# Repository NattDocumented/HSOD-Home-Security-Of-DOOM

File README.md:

# H.S.O.D. : Home Security Of DOOM

A simple home security alarm with personality and a little twist ***wink*** ***wink***.

## What is it?

It is just like your simple, ordinary home security/alarm system. If you input your PIN to arm or disarm the alarm, and if you proceed to enter your PIN just in time, the alarm won't go off. However, when H.S.O.D went off... It doesn't just play a normal alarm... I will scare the burglar away (hopefully)... it plays a pre-recorded audio which you can customize/add custom audio to your liking, of how you would like to torment your burglar.

My personal option is DOOM ETERNAL MUSIC INTRO with + "so you are the chosen one."

## How do you use it?

It is very simple, here's how to use it!

### 1. Arming the Device
* **Action:** On boot, the system is disarmed. Input the PIN.
* **Outcome:** The current state of the device will change from unarmed to armed, and the OLED display and an audio cue from the speaker will indicate that!

### 2. INTRUDER ALERT!!!
* **Action:** Human detected.
* **Outcome:** The device enters a warning state or a countdown state, to be exact. The OLED display and a countdown coming from the speaker tracking your remaining time will also indicate that!

### 3. Disarming the Device
* **Action:** Input the PIN.
* **Outcome:**
  * **Correct PIN:** Everything resets and goes back to normal (back to the unarmed/disarmed state), the OLED display and the sound cue will also indicate it as well!
  * **Incorrect PIN:** Everything continues, but you can still go ahead and try again until the countdown reaches zero (but there's also a max attempt)

## System Architecture

```mermaid

graph TD;
  %%Define styles
  classDef controller fill:
  classDef sensor fill:
  classDef output fill:
  classDef cloud fill:

  %% Nodes
  Radar[HLK-LD2410C]:::sensor
  Mic[ICS-43434]:::sensor
  Keypad[Keypad]:::sensor

  MCU[Arduino Nano ESP32]:::controller

  OLED[OLED Display]:::output
  DFPlayer[DFPlayer Mini + Speaker]:::output

  Wit[Wit.ai Speech API]:::cloud

  %% Connections
  Radar --> |UART2 / Pin D11 Trigger| MCU
  Mic --> | I2S Mono PCM via DMA | MCU
  Keypad --> |Digital I/O Pins 2-8| MCU

  MCU --> |Hardware I2C| OLED
  MCU --> |Hardware UART1| DFPlayer
  MCU -.-> |Chunked HTTPS POST| Wit

```

## State Machine

```mermaid

stateDiagram-v2
  [*] --> STATE_DISARMED : Boot

  STATE_DISARMED --> STATE_ARMED : Enter PIN + ENT

  STATE_ARMED --> STATE_COUNTDOWN : Human Detected

  STATE_COUNTDOWN --> STATE_DISARMED : Correct PIN / Voice Phrase <br> Entered 
  STATE_COUNTDOWN --> STATE_ALARM : Timer Hits 0

  STATE_ALARM --> STATE_DISARMED : Correct PIN / Voice Phrase <br> Entered 
  STATE_ALARM --> STATE_LOCKED_OUT : Too Many Failed Attempts

  STATE_LOCKED_OUT --> STATE_ARMED  

```

## Why did I make it?

Here's a little back story. I passed an entrance exam to one of the best high schools in Thailand (Triam Udom Suksa School, btw ***wink*** ***wink***), which means I have to move away and live alone in the big city, but, being a country boy, I came up with an idea. Wouldn't it be so fitting to add some security measures to my apartment because I'm living alone? Normal Securities are boring, corporate, no personality, there's nothing interesting, so I came up with something new of my own! I came up with this!

## Step-By-Step Build Guide.

### Tools Required
* **Soldering Iron & Solder Wire** 
* **Wire Flush Cutters**
* **Tweezers**

---

### [1] : Prep Your MicroSD Card

1. Insert your **MicroSD card** into your computer and format it to **FAT32**.
2. Drop your custom audio files inside (`0001.mp3`, `0002.mp3`, etc.)
   
   *  `0001.mp3` = Warning beep
   *  `0002.mp3` = Full alarm audio
   *  `0003.mp3` = Armed sound
   *  `0004.mp3` = Disarmed sound
   *  `0005.mp3` = Incorrect sound
   *  `0006.mp3` = Locked out sound
   *  `0007.mp3` = Startup sound

3. Eject the card and insert it right into the slot of the **DFPlayer Mini (U3)**.

### [2] : Soldering Components

This is fairly simple due to each component having its own designated spots on the board; simply find those and solder them in place.

**For Example/Demonstration:**
1. **Keypad:** Insert the 12 **Cherry MX Mechanical Switches (SW1 to SW12)** into the **big key grid squares** on the board. If you can't see it, I'm going to assume you're blind (I'm just playing with ya lol), flip it over, and solder, **simple!**
2. **Modules:** as stated, the OLED Display, Arduino Nano ESP32, HLK-LD2410C, and all the components and modules all have their own slot, just insert them into their own spot, **flip 'em over, and solder!** **simple!**

I think you get it now, simple! Isn't it?
All you have to do is do the same thing for every component of this device.

**Tips, but kind of necessarily:** After soldering everything, use your **Wire Flush Cutters** to cut the excess leads or pins off.

### [3] : Uploading Firmware (PlatformIO)

This project is built using **PlatformIO** which is inside of VS Code instead of the standard Arduino IDE. Here's how to flash the firmware:

#### 1. Clone the Project

```bash
git clone https://github.com/NattDocumented/HSOD-Home-Security-Of-DOOM.git
```

#### 2. Open in VS Code
1. Launch **Visual Studio Code**.
2. Make sure you have the **PlatformIO IDE** extension installed; if not, go ahead and install it.
3. Click `File` > `Open Folder...` from the top menu, navigate to the folder you just cloned, and click **Open**. (Make sure you open the root folder containing the `platformio.ini` file)

#### 3. Making Voice Unlock Works

1. Login to [Wit.ai](https://wit.ai) with your Meta (a.k.a. Facebook) account.
2. If done correctly, it should lead you to the dashboard/apps, if not [click this](https://wit.ai/apps).
3. Click **+ New App** to create a new app **(obviously)**. You can name it whatever you please, but I personally just named it `"hsod"`.
4. Go into your newly created app. You'll see a sidebar. Click on **Management**, and go to **Settings**.
5. Copy your **Client Access Token** and replace these line in the firmware's code.
   
    ```cpp
    const char* WIFI_SSID = "YOUR_WIFI_SSID"; // Your WiFi's SSID
    const char* WIFI_PASS = "YOUR_WIFI_PASSWORD"; // Your WiFi Password here
    const char* WIT_TOKEN = "YOUR_WIT_AI_TOKEN"; // Your Wit.ai's token here
    ```

#### 4. Build and Upload
1. Connect a USB-C data cable from your computer into your Arduino Nano ESP32 port.
2. Click the **PlatformIO Alien Icon** on the left menu bar.
3. Under the Project Tasks menu, click **Build** to compile the codebase.
4. Once the terminal displays a green `[SUCCESS]` message, click **Upload** right below it to flash the firmware onto your board.

#### 5. Done
As soon as the upload completes, the OLED screen will wake up, and the speaker will play the system startup sound.

### [4] : Casing / Enclosure

After finishing the other steps, I think this one is the easiest, so don't be tired yet, lmao.

1. **Have your 3D printed casing / Enclosure ready:** if you haven't done that, go ahead and print it, no rush, because this README.md can't run away from you lmao.
2. **Assemble:** This is easy. There should be 2 parts: the base and the lid. Since there are poles on the base and holes on the PCB for assembly, simply insert the PCB into the enclosure while making sure the USB of the Arduino Nano ESP32 is right where the hole for the USB on the casing is. After, just put the base and lids together while making sure all the components that should be visible are visible. Both the base and the lid have sockets for connecting to each other.
3. **Done!**

#### You can now enjoy this amazing device. Hope you have a great experience. Any feedback is appreciated.

## Gallery

### Finished Product Renders

### Schematics

### PCBs

### Casing / Enclosure Design

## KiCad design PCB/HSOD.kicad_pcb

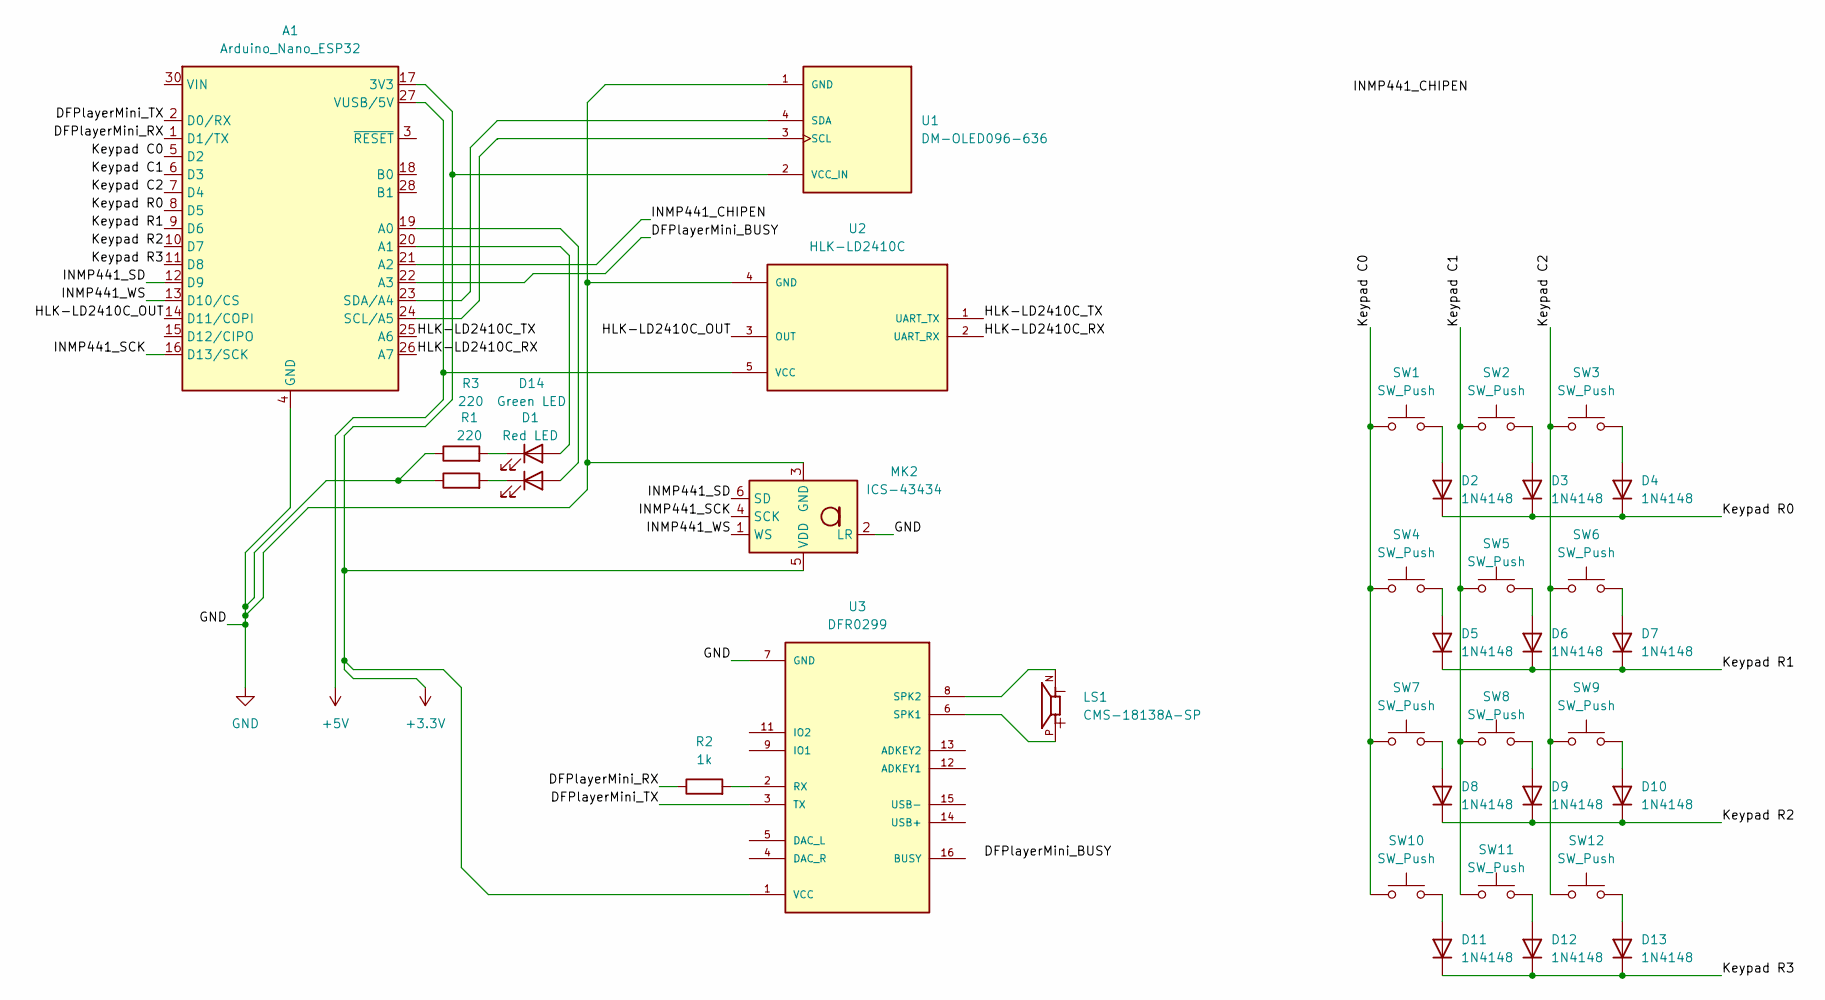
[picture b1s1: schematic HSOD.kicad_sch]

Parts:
A1: Arduino_Nano_ESP32; Arduino_Nano
D1: Red LED; LED_1206_3216Metric
D2, D3, D4, D5, D6, D7, D8, D9, D10, D11, D12, D13: 1N4148; D_DO-35_SOD27_P7.62mm_Horizontal
D14: Green LED; LED_1206_3216Metric
LS1: CMS-18138A-SP; CUI_CMS-18138A-SP
MK2: ICS-43434; InvenSense_ICS-43434-6_3.5x2.65mm
R1, R3: 220; R_1206_3216Metric
R2: 1k; R_1206_3216Metric
SW1, SW2, SW3, SW4, SW5, SW6, SW7, SW8, SW9, SW10, SW11, SW12: SW_Push; SW_Cherry_MX_1.00u_PCB
U1: DM-OLED096-636; MODULE_DM-OLED096-636; PARTREV 2018-09-10
U2: HLK-LD2410C; MODULE_HLK-LD2410C; PARTREV V1.00
U3: DFR0299; MODULE_DFR0299

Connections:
+3.3V: A1.17 (3V3), MK2.5 (VDD), U1.2 (VCC_IN), U3.1 (VCC)
+5V: A1.27 (VUSB/5V), U2.5 (VCC)
/DFPlayerMini_BUSY: A1.22 (A3)
/DFPlayerMini_RX: A1.1 (D1/TX), R2.1
/DFPlayerMini_TX: A1.2 (D0/RX), U3.3 (TX)
/HLK-LD2410C_OUT: A1.14 (D11/COPI), U2.3 (OUT)
/HLK-LD2410C_RX: A1.26 (A7), U2.2 (UART_RX)
/HLK-LD2410C_TX: A1.25 (A6), U2.1 (UART_TX)
/INMP441_CHIPEN: A1.21 (A2)
/INMP441_SCK: A1.16 (D13/SCK), MK2.4 (SCK)
/INMP441_SD: A1.12 (D9), MK2.6 (SD)
/INMP441_WS: A1.13 (D10/CS), MK2.1 (WS)
/Keypad C0: A1.5 (D2), SW1.1, SW4.1, SW7.1, SW10.1
/Keypad C1: A1.6 (D3), SW2.1, SW5.1, SW8.1, SW11.1
/Keypad C2: A1.7 (D4), SW3.1, SW6.1, SW9.1, SW12.1
/Keypad R0: A1.8 (D5), D2.1 (K), D3.1 (K), D4.1 (K)
/Keypad R1: A1.9 (D6), D5.1 (K), D6.1 (K), D7.1 (K)
/Keypad R2: A1.10 (D7), D8.1 (K), D9.1 (K), D10.1 (K)
/Keypad R3: A1.11 (D8), D11.1 (K), D12.1 (K), D13.1 (K)
GND: A1.4 (GND), A1.29 (GND), MK2.2 (LR), MK2.3 (GND), R1.1, R3.1, U1.1 (GND), U2.4 (GND), U3.7 (GND), U3.10 (GND)
unnamed: A1.19 (A0), D1.2 (A)
unnamed: A1.20 (A1), D14.2 (A)
unnamed: A1.24 (SCL/A5), U1.3 (SCL)
unnamed: A1.23 (SDA/A4), U1.4 (SDA)
unnamed: D1.1 (K), R1.2
unnamed: D2.2 (A), SW1.2
unnamed: D3.2 (A), SW2.2
unnamed: D4.2 (A), SW3.2
unnamed: D5.2 (A), SW4.2
unnamed: D6.2 (A), SW5.2
unnamed: D7.2 (A), SW6.2
unnamed: D8.2 (A), SW7.2
unnamed: D9.2 (A), SW8.2
unnamed: D10.2 (A), SW9.2
unnamed: D11.2 (A), SW10.2
unnamed: D12.2 (A), SW11.2
unnamed: D13.2 (A), SW12.2
unnamed: D14.1 (K), R3.2
unnamed: R2.2, U3.2 (RX)
unnamed: LS1.P, U3.6 (SPK1)
unnamed: LS1.N, U3.8 (SPK2)

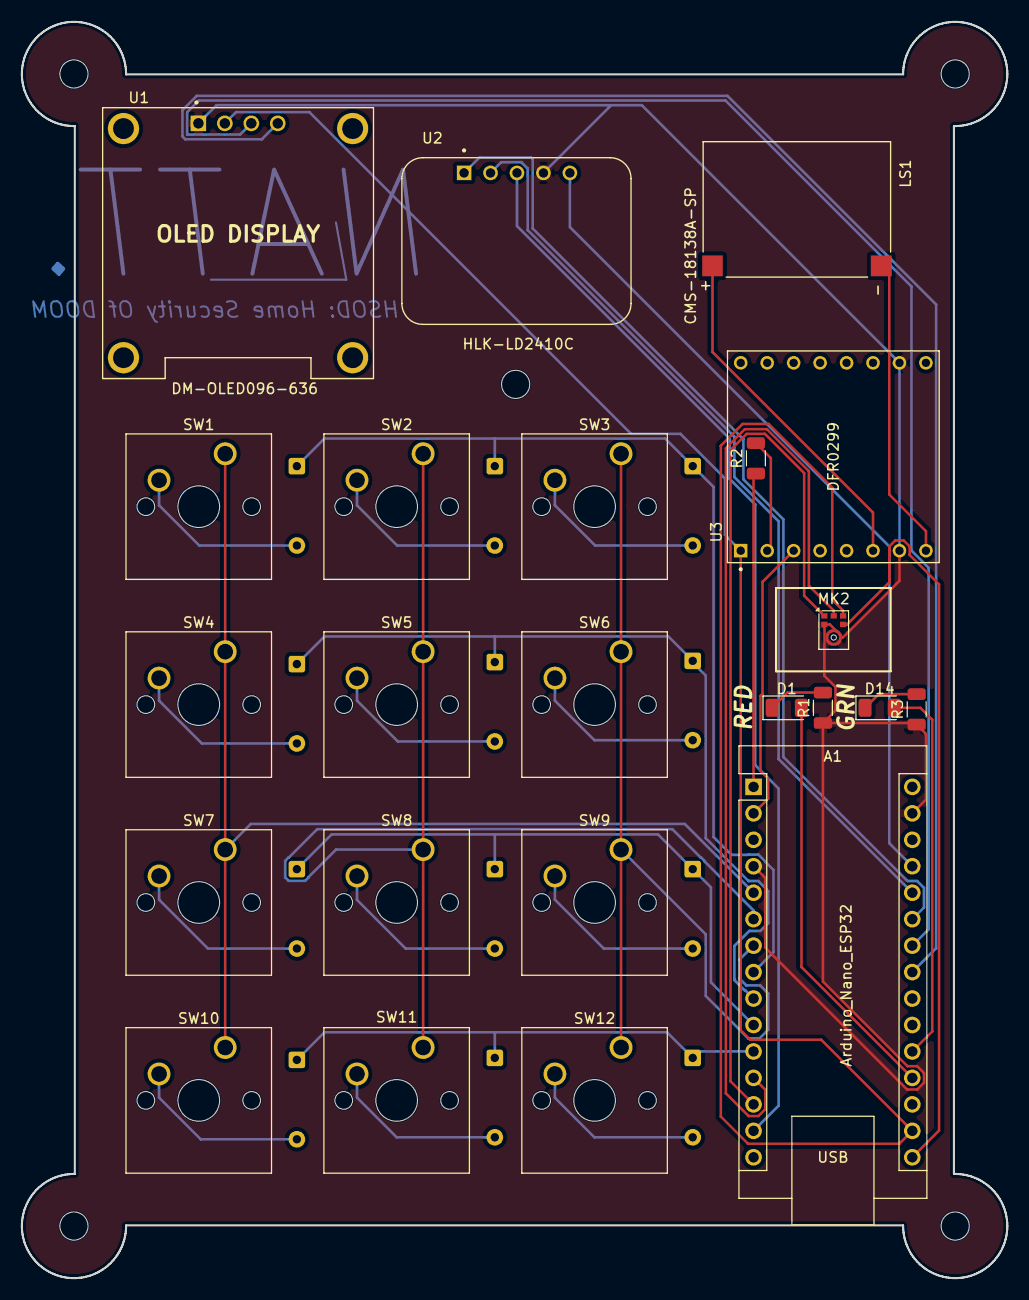
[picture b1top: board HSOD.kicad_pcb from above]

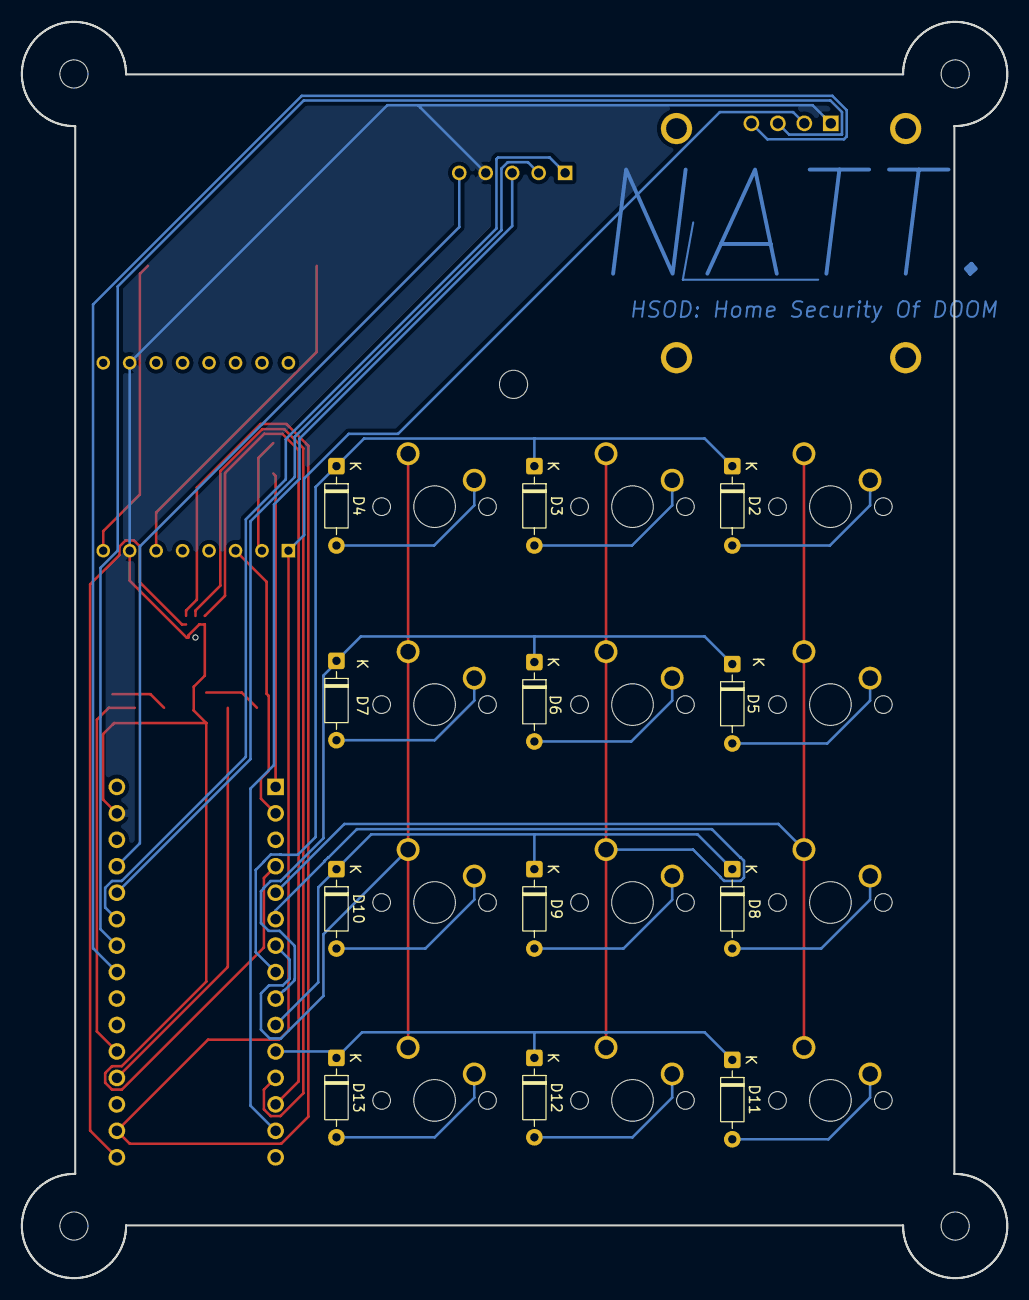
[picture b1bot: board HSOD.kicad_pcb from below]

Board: 2 copper layers, 94.6 x 120.6 mm, 35 parts (12 on the bottom side), 39 nets.

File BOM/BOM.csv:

"Reference","Qty","Value","DNP","Exclude from BOM","Exclude from Board","Footprint","Datasheet"
"A1","1","Arduino_Nano_ESP32","","","","Module:Arduino_Nano","https://docs.arduino.cc/resources/datasheets/ABX00083-datasheet.pdf"
"D1","1","Red LED","","","","LED_SMD:LED_1206_3216Metric",""
"D2,D3,D4,D5,D6,D7,D8,D9,D10,D11,D12,D13","12","1N4148","","","","Diode_THT:D_DO-35_SOD27_P7.62mm_Horizontal","https://assets.nexperia.com/documents/data-sheet/1N4148_1N4448.pdf"
"D14","1","Green LED","","","","LED_SMD:LED_1206_3216Metric",""
"LS1","1","CMS-18138A-SP","","","","CMS-18138A-SP:CUI_CMS-18138A-SP",""
"MK1","1","INMP441ACEZ-R7","","","","INMP441ACEZ-R7:MIC_INMP441ACEZ-R7",""
"R1,R3","2","220","","","","Resistor_SMD:R_1206_3216Metric",""
"R2","1","1k","","","","Resistor_SMD:R_1206_3216Metric",""
"SW1,SW2,SW3,SW4,SW5,SW6,SW7,SW8,SW9,SW10,SW11,SW12","12","SW_Push","","","","Button_Switch_Keyboard:SW_Cherry_MX_1.00u_PCB",""
"U1","1","DM-OLED096-636","","","","Oled from idk 001:MODULE_DM-OLED096-636",""
"U2","1","HLK-LD2410C","","","","HLK-LD2410C:MODULE_HLK-LD2410C",""
"U3","1","DFR0299","","","","DFR0299:MODULE_DFR0299",""

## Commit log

2026-06-10 Initial commit
    Commit to kickstart the repo
2026-06-10 PCBs related
2026-06-13 Add README.md
2026-06-14 Add PIN required for arming
2026-06-16 Add Zine
2026-06-17 Update BOM
2026-06-17 BOM Details
2026-06-17 Add CAD source files
2026-06-17 Added Step-By-Step Build Guide in README.md
2026-06-17 Format BOM.csv
2026-06-20 Added Wit.ai Instructions
2026-06-28 SHIPPING HOTFIX: README.md, HSOD_CASING.step
2026-06-28 Renders with keycaps
